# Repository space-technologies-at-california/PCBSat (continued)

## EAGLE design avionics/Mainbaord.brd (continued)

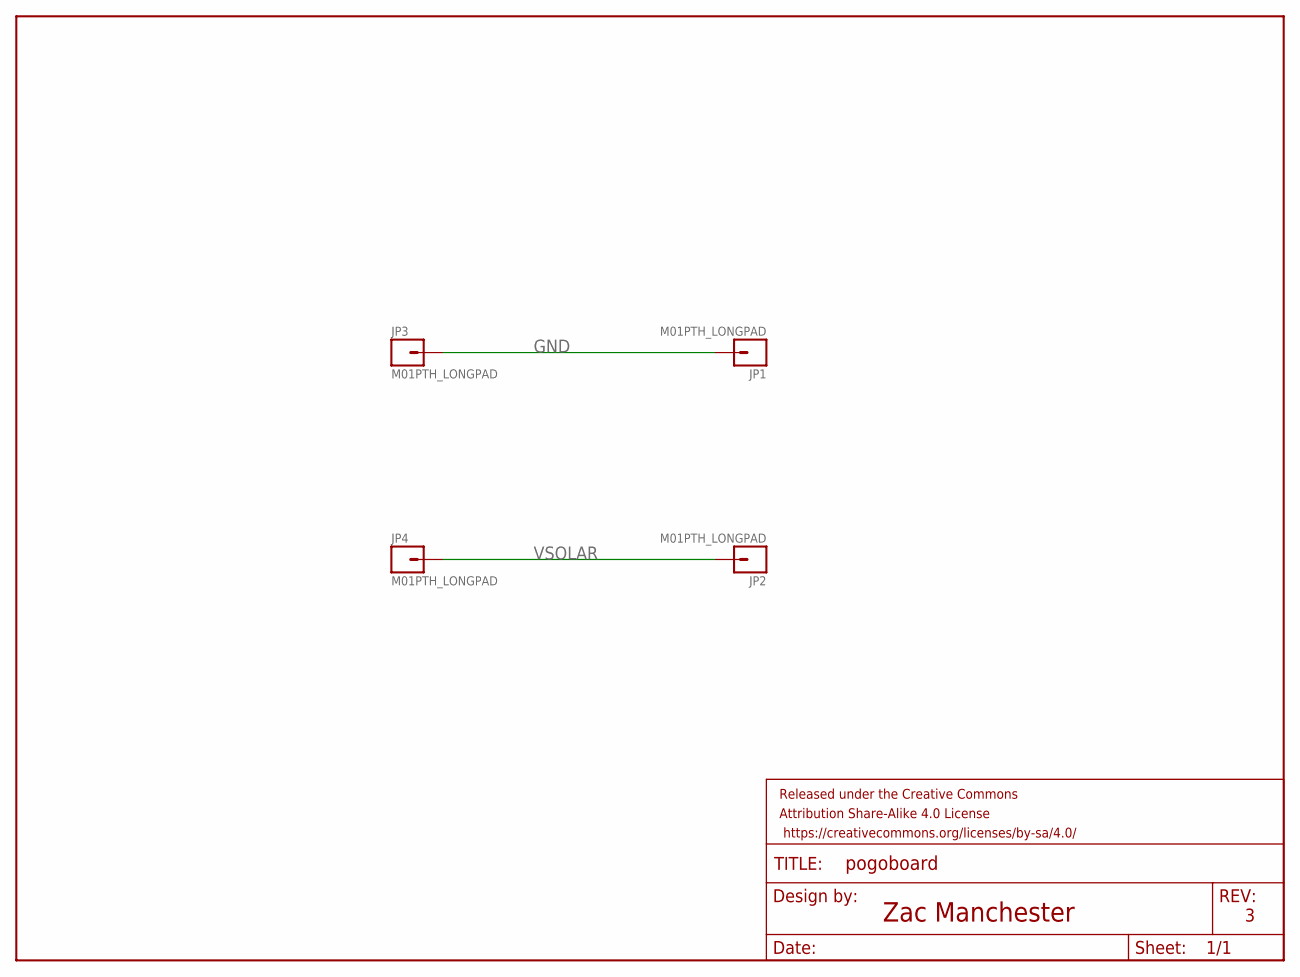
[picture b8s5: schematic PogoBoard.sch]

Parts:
FRAME1: FRAME-LETTER; CREATIVE_COMMONS
JP1, JP2, JP3, JP4: M01PTH_LONGPAD; 1X01_LONGPAD

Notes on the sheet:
Zac Manchester

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
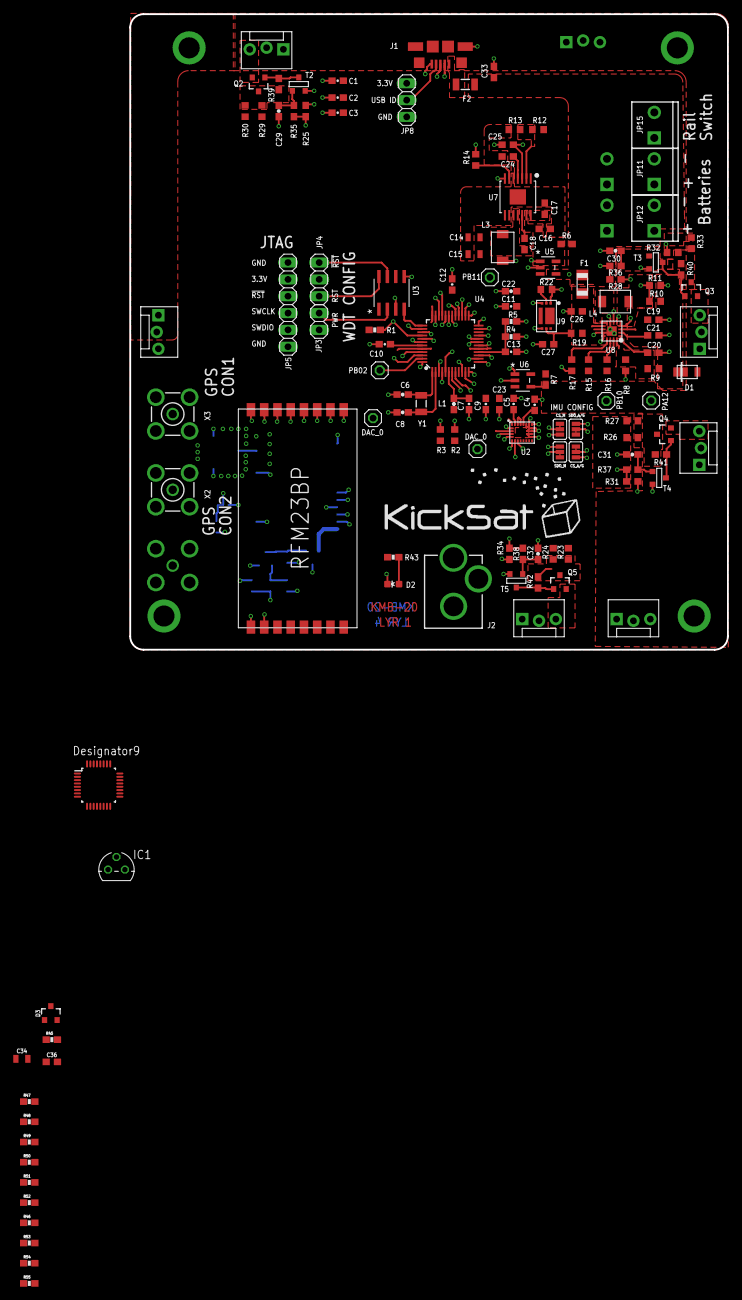
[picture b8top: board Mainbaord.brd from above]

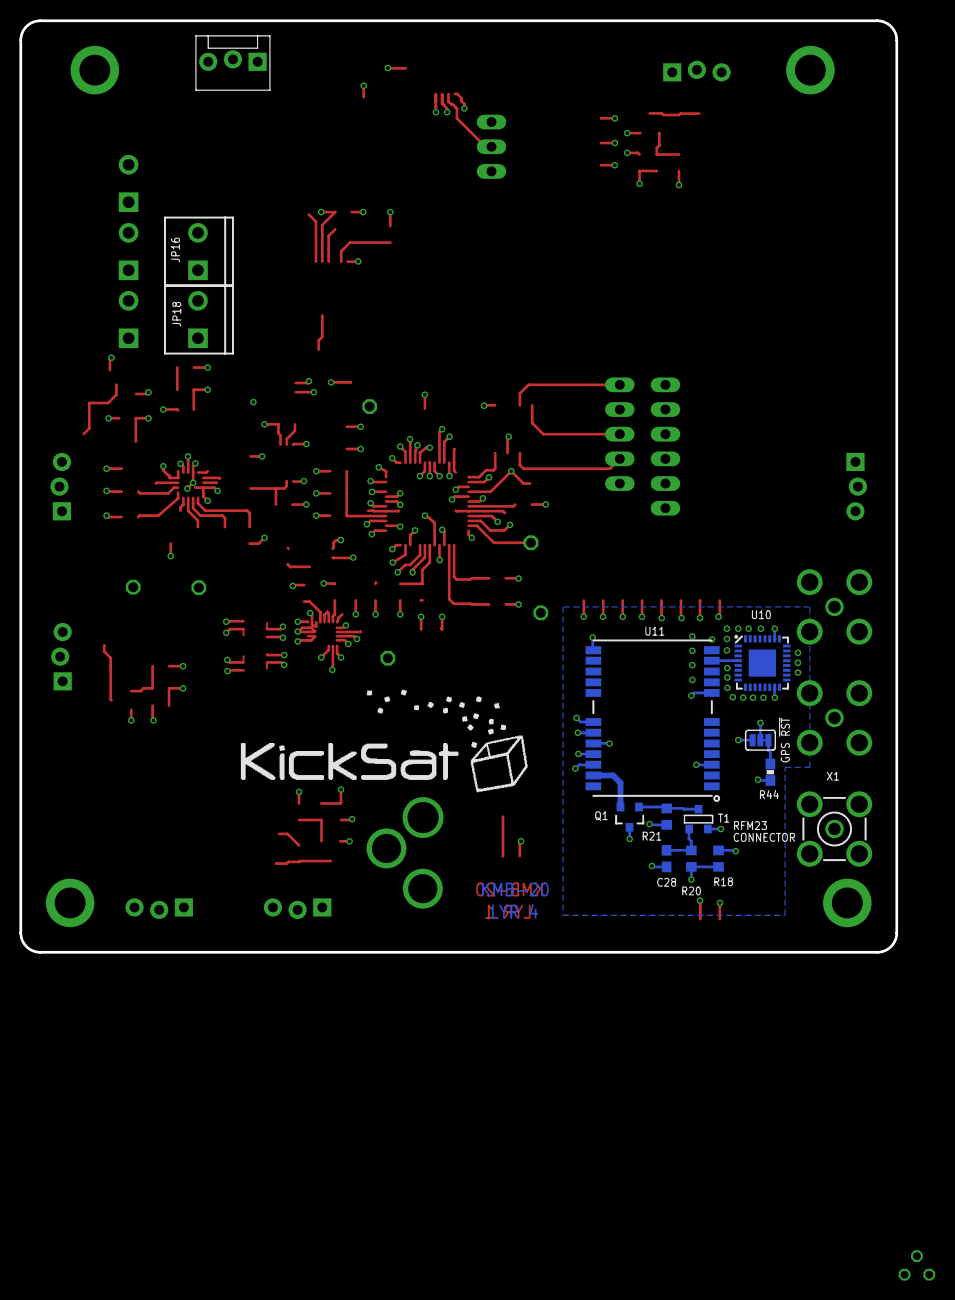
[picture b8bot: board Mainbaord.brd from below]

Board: 4 copper layers, 90.2 x 95.9 mm, 160 parts (15 on the bottom side), 113 nets.

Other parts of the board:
L5: KICKSAT_LOGO

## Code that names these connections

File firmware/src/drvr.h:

#pragma once

#include "lsm.h"

enum Driver {
    XAXIS = 0, // EN_3, Spiral inductor
    YAXIS = 1, // EN_2, Back top
    ZAXIS = 2, // EN_1, Back left
};

uint8_t run_actuation(uint8_t axis, int8_t power, struct vec3_s data[static 1]);
void setup_pwm(void);

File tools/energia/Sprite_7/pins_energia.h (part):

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	P1,		     /*  4 - P1.7 */
	P1,          /*  5 - P1.6 */
	P1,          /*  6 - P1.5 */
	NOT_A_PIN,   /*  7 - VCORE */
	NOT_A_PIN,   /*  8 - DVCC */
	P1,          /*  9 - P1.4 */
	P1,          /* 10 - P1.3 */
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	NOT_A_PIN,   /* 26 - RF_XOUT */
	NOT_A_PIN,   /* 27 - AVCC_RF */
	NOT_A_PIN,   /* 28 - AVCC_RF */
	NOT_A_PIN,   /* 29 - RF_P */
	NOT_A_PIN,   /* 30 - RF_N */
	NOT_A_PIN,   /* 31 - AVCC_RF */
	NOT_A_PIN,   /* 32 - AVCC_RF */
	NOT_A_PIN,   /* 33 - R_BIAS */
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	BV(7),	     /*  4 - P1.7 */
	BV(6),       /*  5 - P1.6 */
	BV(5),       /*  6 - P1.5 */
	NOT_A_PIN,   /*  7 - VCORE */
	NOT_A_PIN,   /*  8 - DVCC */
	BV(4),       /*  9 - P1.4 */
	BV(3),       /* 10 - P1.3 */
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	NOT_A_PIN,   /* 26 - RF_XOUT */
	NOT_A_PIN,   /* 27 - AVCC_RF */
	NOT_A_PIN,   /* 28 - AVCC_RF */
	NOT_A_PIN,   /* 29 - RF_P */
	NOT_A_PIN,   /* 30 - RF_N */
	NOT_A_PIN,   /* 31 - AVCC_RF */
	NOT_A_PIN,   /* 32 - AVCC_RF */
	NOT_A_PIN,   /* 33 - R_BIAS */
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
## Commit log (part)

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2018-06-10 bump library version
2018-06-10 started layout and fixed R0402 packages
2018-06-10 some schematic updates
2018-06-11 Placed all components, probably
2018-06-11 hand routed RF_P and RF_N
2018-06-11 updated drc rules
2018-06-11 Eagle autoroute with buried and 2 blind
2018-06-11 did most of the long traces
2018-06-11 more stuff done
2018-06-11 routed some more routes
2018-06-12 more stuff finished
2018-06-13 Add straight edge RS solar cell drawing
2018-06-13 Move dev board model
2018-06-13 moved all 3 drivers to the bottom side, removed the need for using interlayers and decreased the total number of vias
2018-06-13 added new trisol footprint to layout
2018-06-14 Finishing up more of the Layout
2018-06-16 Fix inductor
2018-06-16 Remove extra test point
2018-06-16 Clean up traces
2018-06-17 Fix footprints and layout
2018-06-17 More routing, removed some vias from the bottom layer
2018-06-17 spiral inductor that can actually be fab'd
2018-06-17 more routes fixed, removed some vias
2018-06-17 Fixing pgood renaming
2018-06-17 Fix TrisolX solar cell courtyard
2018-06-17 Remove pours over PCB inductor
2018-06-17 Add logo
2018-06-17 Add production files
2018-06-18 Changed resistor values
2018-06-18 updated resistitator values again
2018-06-18 Import TI RF example
2018-06-18 Import MSPGCC toolchain
2018-06-18 Adding Zac's libraries
2018-06-18 added spice decks for solar cell simulation
2018-06-18 Add blinky LED
2018-06-18 Remove extra copy of blink
2018-06-18 Add CXX macro
2018-06-18 Add msp430.mk.inc and update README
2018-06-19 Move RF example
2018-06-19 Remove old Energia libraries
2018-06-20 Build RadioBeacon
2018-06-27 Change submodule URL
2018-06-27 Support GNU Make 3.82
    macOS has an old version of GNU Make that does not support shell
    expansion assignment via '!='. Consequently, fall back to the least
    common denominator and break compatibility with other Make's.
2018-06-27 Rename entry point to sprite_main
2018-06-27 Replace sprite_main with RadioData example
2018-06-27 Add note about tenting vias
2018-06-29 Improve blink example
2018-06-29 Update schematic title block matter
2018-06-29 Re-center schematic
2018-06-29 Update values from schematic
2018-06-29 Update fab drawing
2018-06-30 Update blink for new board
2018-07-01 Track core fixes needed for sprite_main to work
2018-07-01 Blink twice before transmitting
2018-07-01 Use SYSTEM_CLK_FREQ
2018-07-01 Bring up UART
2018-07-01 Include Git revision
2018-07-01 Add Wire library
2018-07-01 Fix gitrev.h build
2018-07-01 simple lsm code
2018-07-01 sprite pwm updated
2018-07-01 updating all the submodules to clean up git
2018-07-01 some updates to pins.h
2018-07-01 Add ground vias
2018-07-01 Fix inductor test points
2018-07-01 Add linker flags to GC sections
2018-07-02 Fix size of R10
2018-07-02 Reduce solar cell rectangle size
2018-07-02 Bump revision
2018-07-02 Add STAC decals
2018-07-02 did some nephew tier routing, but added optional 0ohm resistor between Pgood and RST
2018-07-04 explicitly set REGD0 and REGD1 low
2018-07-04 moved stuff around
2018-07-05 fixed makefile
2018-07-05 preliminary add of pins.c and pwm.c
2018-07-05 more pins stuff, some pwm stuff
2018-07-05 main modifications
2018-07-05 fixed compilation issues part 2
2018-07-05 removed old pwm cpp file
2018-07-05 added i2c code
2018-07-05 fixing broken pins.h file
2018-07-05 fixed merge issues
2018-07-06 making makefile also remove generated .map file
2018-07-06 Port radio firmware to C
2018-07-06 Update right gitignore
2018-07-06 added cc430 uart code
2018-07-06 Add deep_sleep() and blink LED with LPM4
2018-07-06 Reorganize
2018-07-06 Fix permissions
2018-07-06 Replace delayMicroseconds() with LPM0 sleep
2018-07-06 Fix use of uninitialized variable
2018-07-06 Blink twice on power up
2018-07-06 Move HPRM to main and radio init to radio_init()
2018-07-06 Initialize radio
2018-07-06 Do not change MCLK frequency
2018-07-06 Declare radio-only functions static
2018-07-06 Add prototypes for main.c
2018-07-06 Re-add delay between bytes
2018-07-08 uart code that doesn't work
2018-07-08 minor modifications to i2c but still not workign
2018-07-09 Move UART and LSM init functions out of init_core()
2018-07-09 fixed F_CPU
2018-07-09 Set GIE in init_core()
2018-07-09 Add power check and interrupts
2018-07-10 Blink LED on UART only when DEBUG_UART is set
2018-07-10 Give FLL time to settle
    This was causing problems with UART right after startup.
2018-07-10 Print gitrev to UART
2018-07-11 Sort includes
2018-07-11 Add state variable in .infoB
2018-07-11 Count number of power cycles
2018-07-11 Use struct missioninfo
2018-07-11 Use sizeof(struct missioninfo)
2018-07-12 Update uart print statements
2018-07-12 removed useless stuff from pins.c and pins.h
2018-07-14 Add state machine mechanics
2018-07-15 Add missing include
2018-07-15 Cast pointers
2018-07-15 test code for flash writes
2018-07-16 Flash next state before running state_main()
2018-07-22 Fixed i2c and lsm transactions
2018-07-22 Declare uart_write* functions const
2018-07-22 Clean up LSM data printing
2018-07-22 initial version of battery code
2018-07-22 Repudiate main_flash()
2018-07-22 Add new flash state recorder
2018-07-23 Changed magnetometer mode for ADC
2018-07-29 adc code
2018-07-30 Add missing ref.h
2018-07-31 Add radio power flag handling
2018-07-31 Pick up only *.c files
2018-07-31 Fixes for lsm interrupt based polling
2018-07-31 Build with DEBUG set
2018-07-31 Move run_* functions to respective source files
2018-07-31 Set interrupts correctly
2018-07-31 Enable interrupts for LSM
2018-08-01 Cosmetic cleanup
2018-08-01 Add preliminary driver control
2018-08-05 switching to using SMCLK
2018-08-05 Turn on regulator
2018-08-05 Fix driver test code
2018-08-09 python code folder initial commit
2018-08-12 Add preliminary interface to mission planner
2018-08-16 Remove legacy
2018-08-18 Update radio register comments
    While here, remove the ones that we didn't check and potentially
    misleading ones. Better to check against datasheet and add them back
    when we need them.
2018-08-23 Save supercap footprint in sprite library
2018-08-23 Dump in a few more supercaps
2018-08-24 added more caps and moved a couple traces
2018-08-24 routes fixed, no DRC violations, 11 new caps
2018-08-24 umac cutout spot
2018-08-24 moving some passives
2018-08-25 fixed silkscreen
2018-08-25 Flipped umac pads
2018-08-25 Flipped umac pads again...stupid avi
2018-08-25 WIP routing w slot
2018-08-25 Added edge cut. Final version probably
2018-08-25 Remove old Engeria support files
2018-08-25 Remove silkscreen logo on back
2018-08-25 Line up slot on grid
2018-08-25 Remove back silkscreen logo
2018-08-25 Promote gitignore
2018-08-25 Add more slot margin and move top logo
2018-08-25 Fix unconnected
2018-09-03 Add PRNs from Zac verbatim
2018-09-09 fixing lsm issue by resetting lsm at every call to setup()
2018-09-09 Add flight PRNs
2018-09-09 Move PRN to separate file
2018-09-10 Run LSM setup only once
2018-09-10 fixing lsm magnetometer code, by reseting the ctrl_reg3_m
2018-09-10 Stop rebooting XL
2018-09-10 Use reasonable data types
2018-09-10 Nail down argument
2018-09-10 Stop rebooting magnetometer
2018-09-10 Add missing ref.c
2018-09-10 Clean up header
2018-09-11 add magnetorquer .py file
2018-09-11 Move to correct location
2018-09-11 updates to drv code
2018-09-11 updates to drvr.c
2018-09-12 Hook in battery monitor
2018-09-12 Remove executable bits
2018-09-12 Document batt_voltage
2018-09-12 Check for MPPT failure
    Report inconsistencies between PGOOD and measured battery voltage.
2018-09-12 Stop doing a stupid division
2018-09-12 Stop header file abuse
2018-09-12 Fix warnings
2018-09-12 Remove unused files
2018-09-12 Clean up unused symbols
2018-09-12 Enable WDT
2018-09-12 Pet watchdog
2018-09-12 Document transmission time
2018-09-12 updated battery monitor to also measure and store temperature
2018-09-12 updated lsm code, useless change to drvr only to pull changes
2018-09-12 making drvr functions local
2018-09-12 Add random delay between transmissions
2018-09-12 Keep track of timing through long sleeps
2018-09-12 Make rand_int() function
2018-09-12 Construct message
2018-09-12 added lsm code to find angular acceleration
2018-09-12 Add missing ifdef
2018-09-12 Fix warning
2018-09-12 Separate debug PRN from debug build
2018-09-12 Adjust timing
2018-09-12 updates to blocking lsm and blocking drvr
2018-09-12 fixing compilation issues
2018-09-12 adding final transmit stuff
2018-09-12 Do not attempt to actuate if LSM setup fails
2018-09-13 Flip UMAC connectors and offset coil pad
2018-09-13 Change solder paste
2018-09-13 Add supercap to shared library
2018-09-13 Remove duplicated library
2018-09-13 Point to moved footprint library
2018-09-14 Don't turn off ADC and temp sensor on startup
2018-09-14 Reorder init code
2018-09-14 Make tx_msg global
2018-09-14 Document interrupt clear
2018-09-14 Harden power check
2018-09-14 fixing norm function
2018-09-14 Fix redundant pin setup
2018-09-14 Set GPF if ADC setup fails
2018-09-14 Minor changes to battery monitor
2018-09-14 Make radio use globals
2018-09-14 Remove via-in-pad
2018-09-15 Cap board respin for thinner profile
2018-09-15 Cap board repsin with all nets connected
2018-09-15 Add via to fix layer 3 fill
    While here connect antenna pins to silence unconnected warning.
2018-09-16 moving around traces to create room for the center spiral inductor
2018-09-16 Prepare layout for spiral inductor
2018-09-16 adding proportional bdot control
2018-09-17 updated controller
2018-09-17 fixing some compilation issues
2018-09-17 Route spiral inductor
2018-09-17 updated pcb with spots for 6 more caps
2018-09-17 Adjust silkscreen text and courtyard width
2018-09-17 Clean up silkscreen
2018-09-17 final version
2018-09-17 setup magnetorquer_out in lsm.h
2018-09-18 fixed lsm.h and fixed incorrect directory for firmware download
2018-09-19 Fix edge cut
2018-09-23 added TODOs
2018-09-24 Only operate radio in safe mode
2018-09-24 Reorganize directory structure
2018-09-24 Track dependencies
2018-09-24 Add controller debugging outputs
2018-09-24 Print data output for debug
2018-09-25 Add delay between transmissions
2018-09-25 updated python controller
2018-09-25 fixed dot product
2018-09-25 Split calculations to separate source file
2018-09-25 testing - dont fly
2018-09-26 u int tests
2018-09-26 added testing
2018-09-26 fixed printing
2018-09-26 fixed some values and cleaned up code
2018-10-11 Fixed moving_average fn in calc.c
2018-10-12 Move MOVING_AVG_FILTER_LEN definition
2018-10-12 Add moving average test
2018-10-12 Optimize
2018-10-12 Flip GPF and SAFEMODE bit
    Only the bottom 6 bits of 'faults' get transmitted. GPF is less
    important than SAFEMODE.
2018-10-12 added firmware code on new branch for no torque board - sends mag and gyro data in last 2 bytes
2018-10-12 changed m_data and meas_alpha to int16 - should be 9 bytes now - maybe update char tx_msg
2018-10-13 Add two PRNs
2018-10-13 Remove state recorder
2018-10-14 Update power setting
2018-10-14 Add build configurations for S1-S5
2018-10-14 Correctly include config.h
2018-10-14 Add convenience programming script
2018-10-14 Add Sprite 7
2018-10-14 Remove admonition
2018-10-14 Move norm function
2018-10-14 Add norm test
2018-10-14 Fix conflicting definition
2018-12-19 Initial version of data gen for tf experiments
2018-12-20 updated tf_data_gen
2018-12-21 updated generating g_data
2018-12-21 Created script iss_loc.py that will generate 10800 seconds (3 hours) of timestamp, latitude, longitude data
2018-12-21 Ran iss_loc.py script for 9 hours and stored data into iss_loc_data_1545365126.csv. iss_loc_data_1545364972.csv is just a test file
2018-12-21 added constant gyro data
2018-12-21 Update README.rst
    Added information about new simulation data creation scripts
2018-12-23 Update README.rst
    consolidated data generation files
2018-12-23 Changed gyro data to be in radians/s instead of deg/s
2019-01-01 added method for unique random init of gyro data - still axis=1 issue
2019-01-01 Added offset to mag_x. Full_ files have gyro data that is the same for all rows. fullunique_ files have gyro data that is unique to each row.
2019-01-03 Added prediction output to compare against truth and save models within model_dir location for use in tensorboard
2019-01-13 updated power and axis model
2019-01-28 tested torque
2019-01-28 added note on time that we need to fix
2019-02-18 KRR implemented
